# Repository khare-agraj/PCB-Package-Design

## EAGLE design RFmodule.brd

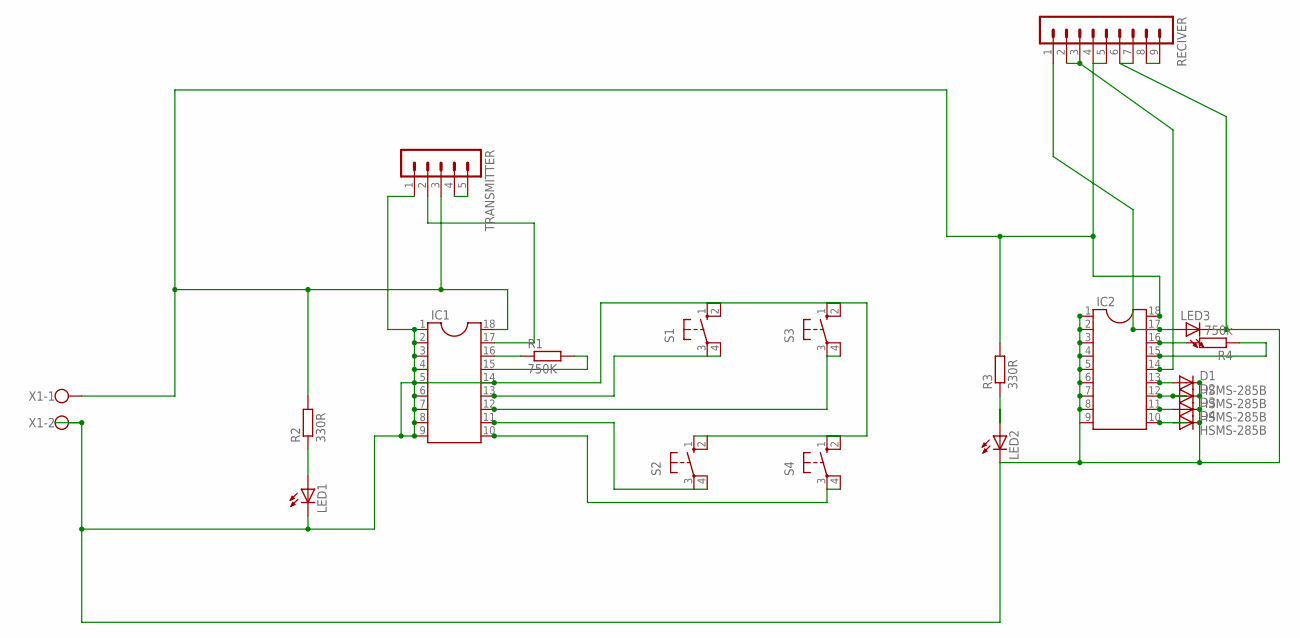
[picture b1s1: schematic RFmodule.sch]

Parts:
D1, D2, D3, D4: HSMS-285B; SOT323
IC1, IC2: DIL18
LED1, LED2, LED3: LED5MM
R1: 750K; 0207/10
R2: 330R; 0207/10
R3: 330R; 0204/7
R4: 750k; 0204/7
RECIVER: MA09-1
S1, S2, S3, S4: 10-XX; B3F-10XX
TRANSMITTER: MA05-1
X1: W237-102

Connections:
GND: D1.3 (C), D2.3 (C), D3.3 (C), D4.3 (C), IC1.1, IC1.2, IC1.3, IC1.4, IC1.5, IC1.6, IC1.7, IC1.8, IC1.9, IC1.14, IC2.1, IC2.2, IC2.3, IC2.4, IC2.5, IC2.6, IC2.7, IC2.8, IC2.9, LED1.K (C), LED2.K (C), LED3.K (C), RECIVER.6, RECIVER.7, S1.1 (S), S1.2 (S1), S2.1 (S), S2.2 (S1), S3.1 (S), S3.2 (S1), S4.1 (S), S4.2 (S1), TRANSMITTER.1, X1.2
unnamed: LED2.A, R3.1
unnamed: IC1.13, S1.3, S1.4 (P1)
unnamed: LED1.A, R2.1
unnamed: IC1.16, R1.1
unnamed: IC1.15, R1.2
unnamed: IC1.11, S2.3, S2.4 (P1)
unnamed: D1.1 (A), IC2.13
unnamed: IC1.10, S4.3, S4.4 (P1)
unnamed: IC1.12, S3.3, S3.4 (P1)
unnamed: D2.1 (A), IC2.12
unnamed: D3.1 (A), IC2.11
unnamed: D4.1 (A), IC2.10
unnamed: TRANSMITTER.4, TRANSMITTER.5
unnamed: IC1.17, TRANSMITTER.2
unnamed: RECIVER.8, RECIVER.9
unnamed: IC2.17, LED3.A, RECIVER.1
unnamed: IC2.16, R4.2
unnamed: IC2.15, R4.1
unnamed: IC2.14, RECIVER.2, RECIVER.3
VCC: IC1.18, IC2.18, R2.2, R3.2, RECIVER.4, RECIVER.5, TRANSMITTER.3, X1.1

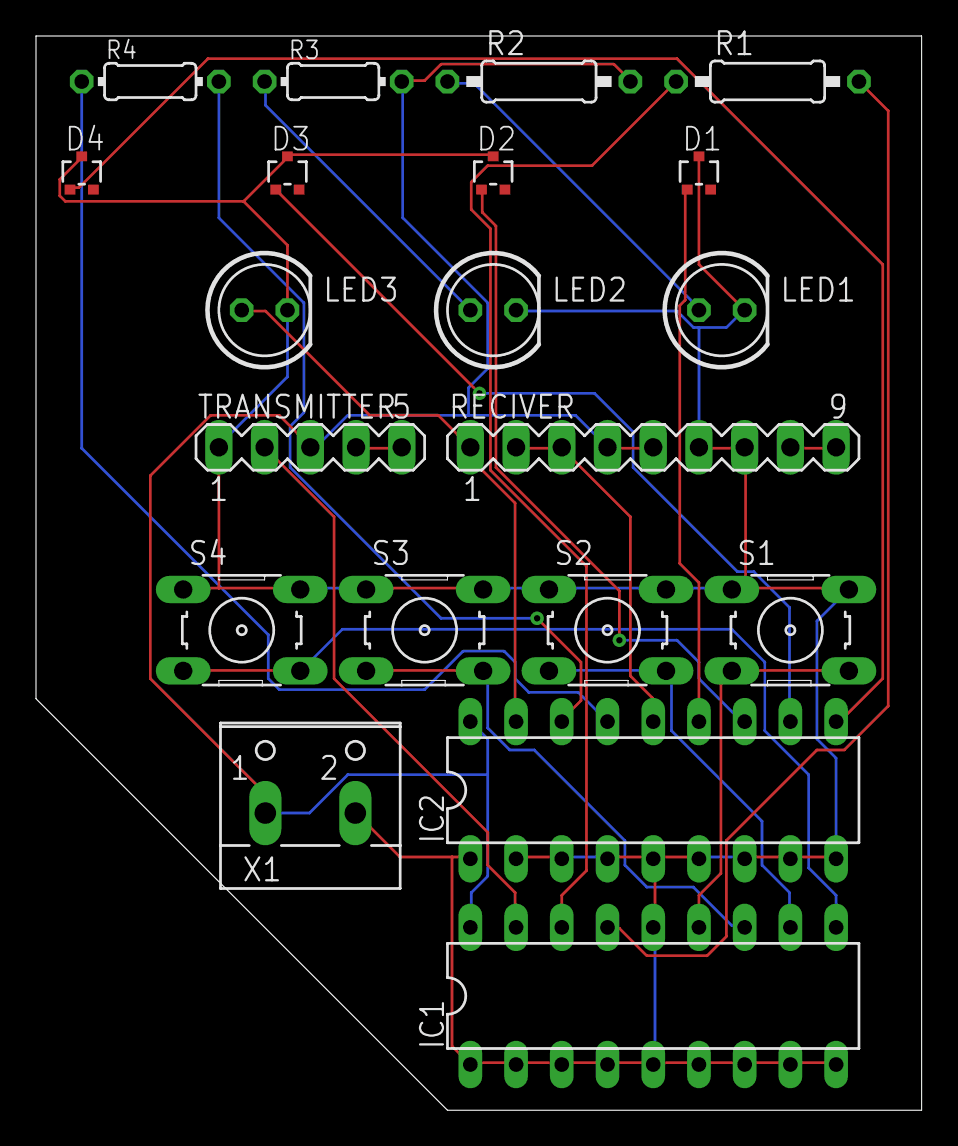
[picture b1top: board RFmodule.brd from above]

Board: 2 copper layers, 49.2 x 59.7 mm, 20 parts (0 on the bottom side), 21 nets.

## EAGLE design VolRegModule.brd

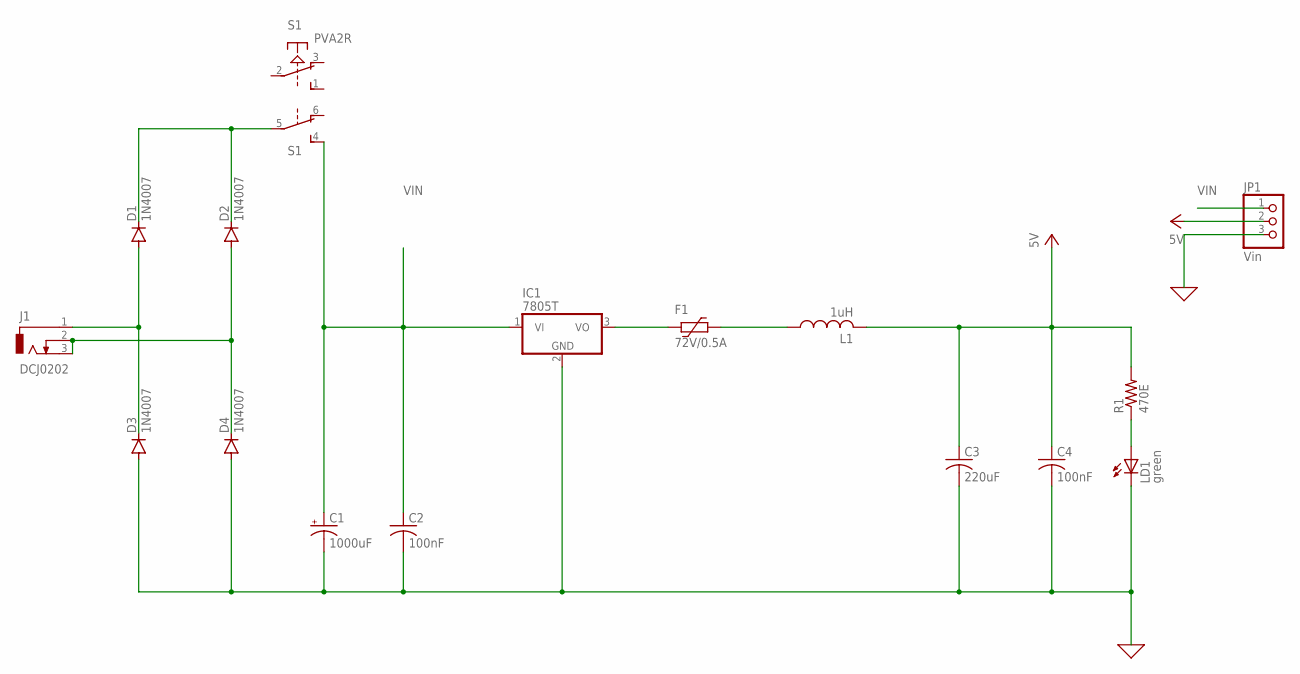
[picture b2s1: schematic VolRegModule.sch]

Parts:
C1: 1000uF; E5-13
C2, C4: 100nF; C0805
C3: 220uF; C0805
D1, D2, D3, D4: 1N4007; DO41-10
F1: 72V/0.5A; 1812L
IC1: 7805T; TO220H
J1: DCJ0202
JP1: Vin; 1X03
L1: 1uH; L0805
LD1: green; CHIP-LED0805
R1: 470E; R0805
S1: PVA2R

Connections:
0: C1.-, C2.2, C3.2, C4.2, D3.A, D4.A, IC1.2 (GND), JP1.3, LD1.C
unnamed: D1.A, D3.C, J1.1
unnamed: D1.C, D2.C, S1.5
unnamed: F1.2, IC1.3 (VO)
unnamed: F1.1, L1.1
unnamed: D2.A, D4.C, J1.2, J1.3
unnamed: LD1.A, R1.1
VCC: C3.1, C4.1, JP1.2, L1.2, R1.2
VIN: C1.+, C2.1, IC1.1 (VI), JP1.1, S1.4 (S)

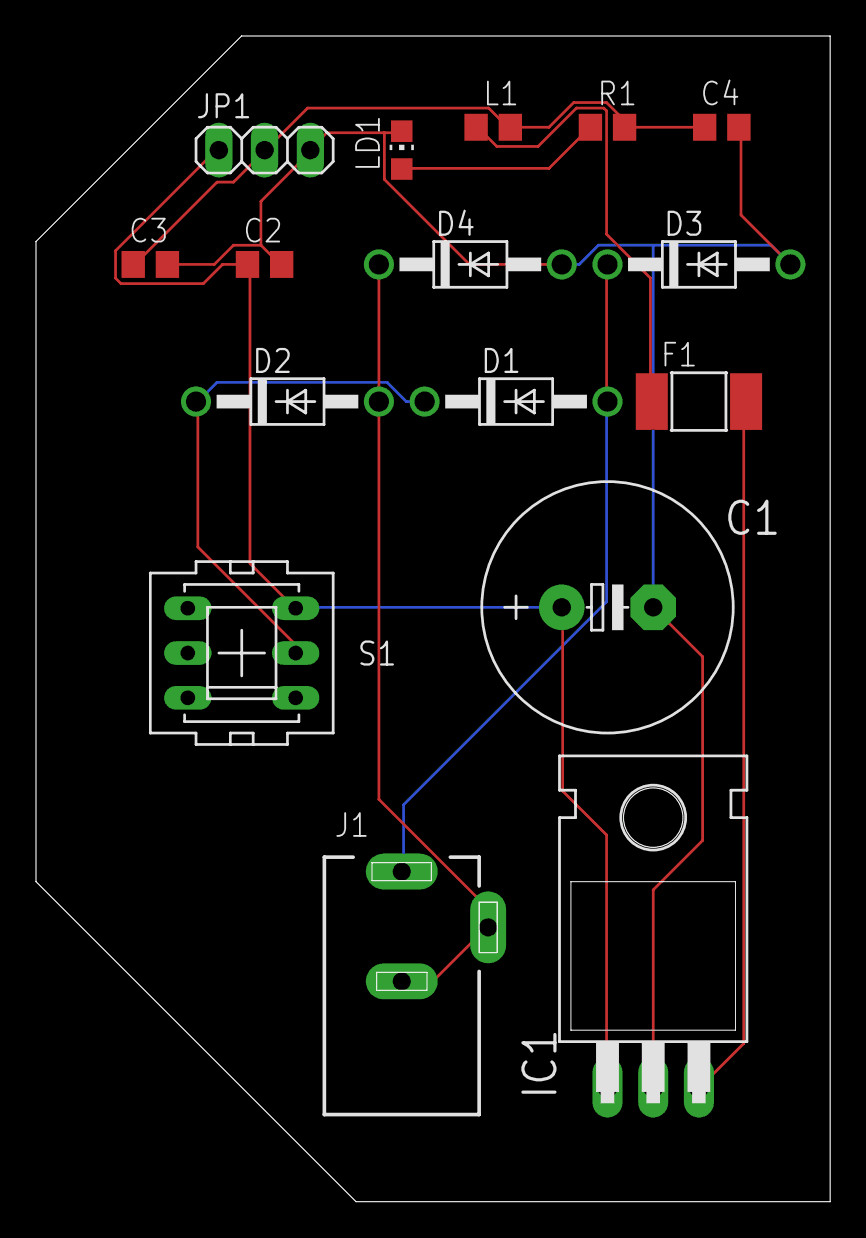
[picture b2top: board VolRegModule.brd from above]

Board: 2 copper layers, 44.1 x 64.8 mm, 16 parts (0 on the bottom side), 9 nets.

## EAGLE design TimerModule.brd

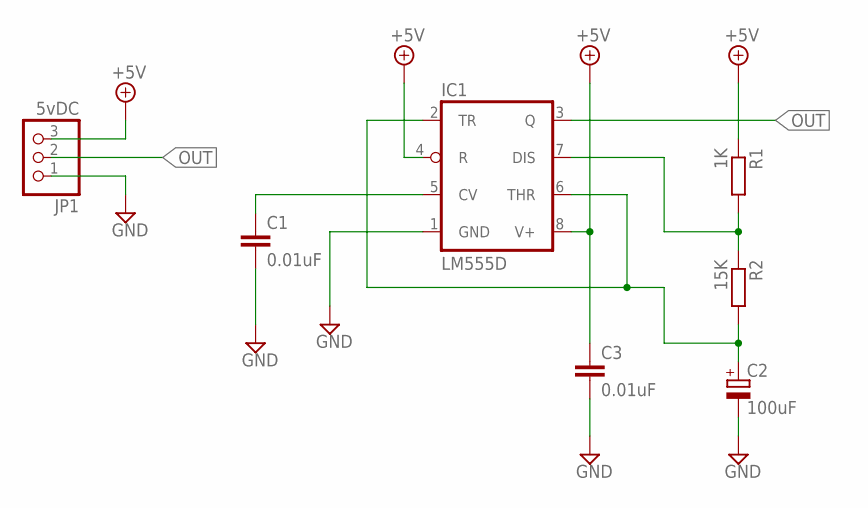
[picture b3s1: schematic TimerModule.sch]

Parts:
C1, C3: 0.01uF; C0805
C2: 100uF; E2,5-5
IC1: LM555D; SO08
JP1: 5vDC; 1X03
R1: 1K; M0805
R2: 15K; M0805

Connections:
+5V: C3.1, IC1.4 (R), IC1.8 (V+), JP1.3, R1.1
GND: C1.2, C2.-, C3.2, IC1.1 (GND), JP1.1
unnamed: C1.1, IC1.5 (CV)
unnamed: IC1.7 (DIS), R1.2, R2.1
unnamed: C2.+, IC1.2 (TR), IC1.6 (THR), R2.2
OUT: IC1.3 (Q), JP1.2

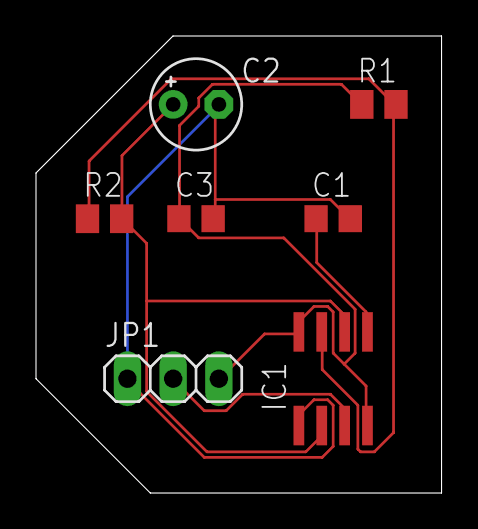
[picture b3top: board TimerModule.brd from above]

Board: 2 copper layers, 22.5 x 25.4 mm, 7 parts (0 on the bottom side), 6 nets.
